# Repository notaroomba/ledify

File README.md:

<h1 align="center">
  <br>
  
</h1>

<h4 align="center">
A super small addressable LED controller with USB-C PD up to 100W, a switchable 5V/12V output and Bluetooth!
</h4>

<div align="center">

</div>

<p align="center">
  <a href="#key-features">Key Features</a> •
  <a href="#pcb">PCB</a> •
  <a href="#firmware">Firmware</a> •
  <a href="#credits">Credits</a> •
  <a href="#license">License</a>
</p>

## Key Features

- **ESP32-C6** microcontroller with Wi-Fi 6 and Bluetooth LE
- **16MB flash** (W25Q128JVP)
- **USB-C PD** up to 100W with the FUSB302B
- **Switchable 5V/12V LED output** from a 10A buck converter (LM61495), selected in software
- **Addressable LED pads** (VCC / SIG / GND) for WS2812B, WS2811 and WS2815 strips
- **IMU and Barometer** - BMI323 (6-axis) and BMP581 pressure sensor
- **Ambient light sensor** (OPT4001) for automatic brightness
- **I2S microphone** (ICS-43434) for sound-reactive effects
- **PCB trace antenna** with an impedance matching network
- **3.3V buck converter** (AP63203) for the logic side
- **ESD protection** on the USB data lines
- **Reset and boot buttons** and a mounting hole
- **4-layer PCB** design with optimized RF layout and routing

## PCB

Designed in KiCad with attention to RF design and high current power delivery. The board is 4 layers with a solid ground plane under the ESP32, the flash and the antenna feed, and the LED buck follows the layout in the LM61495 datasheet.

### Schematic

### Layout

### Pinout

| GPIO | Net        | Function                                  |
| ---- | ---------- | ----------------------------------------- |
| 2    | LED_SW_V   | LED voltage select (low = 5V, high = 12V) |
| 3    | LED_ENABLE | LED buck enable                           |
| 5    | LED_CON    | LED data (SIG pad)                        |
| 6    | MIC_OUT    | Microphone I2S data                       |
| 22   | MIC_CS     | Microphone I2S word select                |
| 23   | MIC_SCK    | Microphone I2S bit clock                  |
| 10   | I2C_SDA    | I2C data (FUSB302B, OPT4001)              |
| 11   | I2C_SCL    | I2C clock (FUSB302B, OPT4001)             |
| 16   | USB_PD_INT | FUSB302B interrupt                        |
| 18   | SPI_MISO   | Sensor SPI                                |
| 19   | SPI_MOSI   | Sensor SPI                                |
| 20   | SPI_SCK    | Sensor SPI                                |
| 21   | CS_IMU     | BMI323 chip select                        |
| 7    | CS_BARO    | BMP581 chip select                        |
| 12   | DN         | USB D-                                    |
| 13   | DP         | USB D+                                    |
| 9    | CHIP_BOOT  | Boot button                               |
| 8    | -          | Strapping pin, pulled up to 3V3           |

### Next revision

Rev 1 works; these are the changes queued for rev 2, each with the reason it is worth a spin of the board.

| Change | Why | How |
| --- | --- | --- |
| Measure the strip current | The power limit and the warnings are arithmetic from the frame; a measurement catches strips that draw more than the model and lets the firmware show real watts | INA226 (I2C, address 0x40 next to the FUSB302 at 0x22 and the OPT4001) with a 2 mΩ 2512 shunt high side on the LED rail after the buck (10 A gives 20 mV, 1 mA resolution; 0.2 W in the shunt). Its VBUS pin reads the rail, so it also sees the 12 V setting. ALERT to GPIO14 for an over-current interrupt |
| Second data output | Two strips from one board, or a strip fed from both ends with the data going into each half | A second SIG pad on GPIO17 (a second RMT channel in firmware). Both outputs through a 74AHCT1G125 each: 3.3 V data into 5 V pixels is out of spec today and works only over short leads |
| 5.2 V setting for long strips | A one-end-fed 5 V strip sags towards the far end and goes warm; starting 0.2 V higher is what long-strip supplies do | 499 kΩ from U6 FB to the drain of a 2N7002, gate from GPIO0 with a 100 kΩ pull-down. In parallel with the 24.9 kΩ bottom resistor it makes 23.7 kΩ, so 1.0 V × (1 + 100/23.7) = 5.22 V on command; the 12 V setting (14.3 kΩ switched in by Q1) is untouched |
| Power injection pads | The real fix for the sag is a second feed into the far end, and it needs a 10 A home on the board | A second VCC/GND pad pair next to the first, both on the wide copper of the LED rail |
| A user button | The BOOT button already toggles the output in firmware, but it sits under the case and shares the strapping pin | A button on GPIO1 with its own pull-up, away from the strapping pins |
| Microphone port | Board 1's ICS-43434 passes the electrical checks but hears nothing: the acoustic port is suspected | Confirm the port hole in the copper and solder mask under the mic, and keep the mic away from the buck inductor |

Free GPIOs after rev 1: 0, 1, 14, 17 (4 and 15 are strapping pins). The feedback network today: 100 kΩ top, 24.9 kΩ bottom, 1.0 V reference, 5.02 V; Q1 adds 14.3 kΩ in parallel for 12.0 V.

### JLCPCB Quote

## Firmware

The firmware in [`firmware/`](firmware/) is an ESP-IDF v6.1 project with drivers for everything on the board: USB-PD negotiation on the FUSB302B, the LED strip, the light sensor, IMU, barometer and microphone. It takes the same text commands from three places: the USB serial console, Bluetooth (it advertises as `Ledify` with the Nordic UART service, so nRF Connect or Bluefruit Connect work) and MQTT. Point it at a Wi-Fi network and a broker and it shows up in Home Assistant on its own as a light with eight effects (solid, rainbow, temperature, spectrum, meter, sound, VU, pulse), an auto-brightness switch, sliders for the pixel count and the sound, light and temperature tunables, a chip-type select and illuminance, temperature, pressure and sound sensors. The colour source, brightness source and overlay can also be mixed freely, so a rainbow VU meter that dims in a dark room is three commands. Brightness is capped automatically to what the USB-PD contract can supply, so a long strip on a laptop port dims instead of browning out.

| Command               | Action                                                                 |
| --------------------- | ---------------------------------------------------------------------- |
| `on` / `off`          | LED buck on or off                                                     |
| `rgb R G B`           | Fills the strip with a color (0-255 each)                              |
| `level N`             | Brightness cap (0-255)                                                 |
| `count N`             | How many pixels to drive (up to 1000, also a slider in Home Assistant) |
| `type ws2812`         | Chip type: `ws2812` (B/C/D/E, WS2813, WS2815), `ws2811`, `sk6812`, `sk6812w`, `ws2816` |
| `mode NAME`           | Preset, also the Home Assistant effect: `solid`, `rainbow`, `temp` (blue-white-red from the temperature), `spectrum` (bass/mid/treble bars), `meter`, `sound`, `vu`, `pulse` |
| `color` / `bright` / `overlay` | Mix your own: colour source, brightness source (`level` or `sound`), overlay (`none`, `vu`, `pulse`) |
| `auto on` / `auto off` | Brightness follows the ambient light sensor, off below a night threshold |
| `gain N`, `lux LO HI`, `night N`, `temp LO HI` | Saved tunables for the sound, light and temperature styles; `temp 21.5` feeds a temperature in |
| `volt 5` / `volt 12`  | Selects the output voltage, turns the output off first. 12V needs a 15V+ PD contract |
| `status`              | JSON with the PD contract, network state, lux, temperature, pressure, motion and sound level |
| `pd` / `net`          | The charger's offered voltages / Wi-Fi and MQTT state                  |
| `wifi SSID PASS`      | Saves the Wi-Fi credentials and restarts                               |
| `mqtt URL USER PASS`  | Saves the broker and restarts                                          |
| `ota URL`             | Updates the firmware over Wi-Fi, with automatic rollback               |

The output always boots at 5V and off, and the board asks the charger for the highest voltage up to 20V as soon as it starts. Credentials, the strip length, the chip type and the tunables are stored in the ESP32's NVS partition, never in the code. SIG is 3.3V logic going to the strip's DIN; the wiring notes, MQTT topics and the Mosquitto-on-Railway broker setup are in [`firmware/README.md`](firmware/README.md).

### Building and flashing

```bash
cd firmware
source ~/.espressif/tools/activate_idf_v6.1.sh
idf.py build
idf.py -p /dev/cu.usbmodem2101 flash monitor
```

## Credits

This project uses:

- [KiCad](https://www.kicad.org/)
- [Blender](https://www.blender.org/) for 3D renders
- [MicroPython](https://micropython.org/)

## You may also like...

- [Cyberboard](https://github.com/NotARoomba/cyberboard) – A Raspberry Pi Pico-sized STM32 development board
- [CyberCard](https://github.com/NotARoomba/CyberCard) – A Cyberpunk themed NFC hacker card
- [Ember](https://github.com/NotARoomba/ember) – USB-C PD Powered Hotplate
- [Trace](https://github.com/NotARoomba/trace) – An ruler for engineers
- [Athena](https://github.com/NotARoomba/athena) – A flight controlelr with a triple MCU architecture

## License

MIT

---

> [notaroomba.dev](https://notaroomba.dev) &nbsp;&middot;&nbsp;
> GitHub [@NotARoomba](https://github.com/NotARoomba) &nbsp;&middot;&nbsp;

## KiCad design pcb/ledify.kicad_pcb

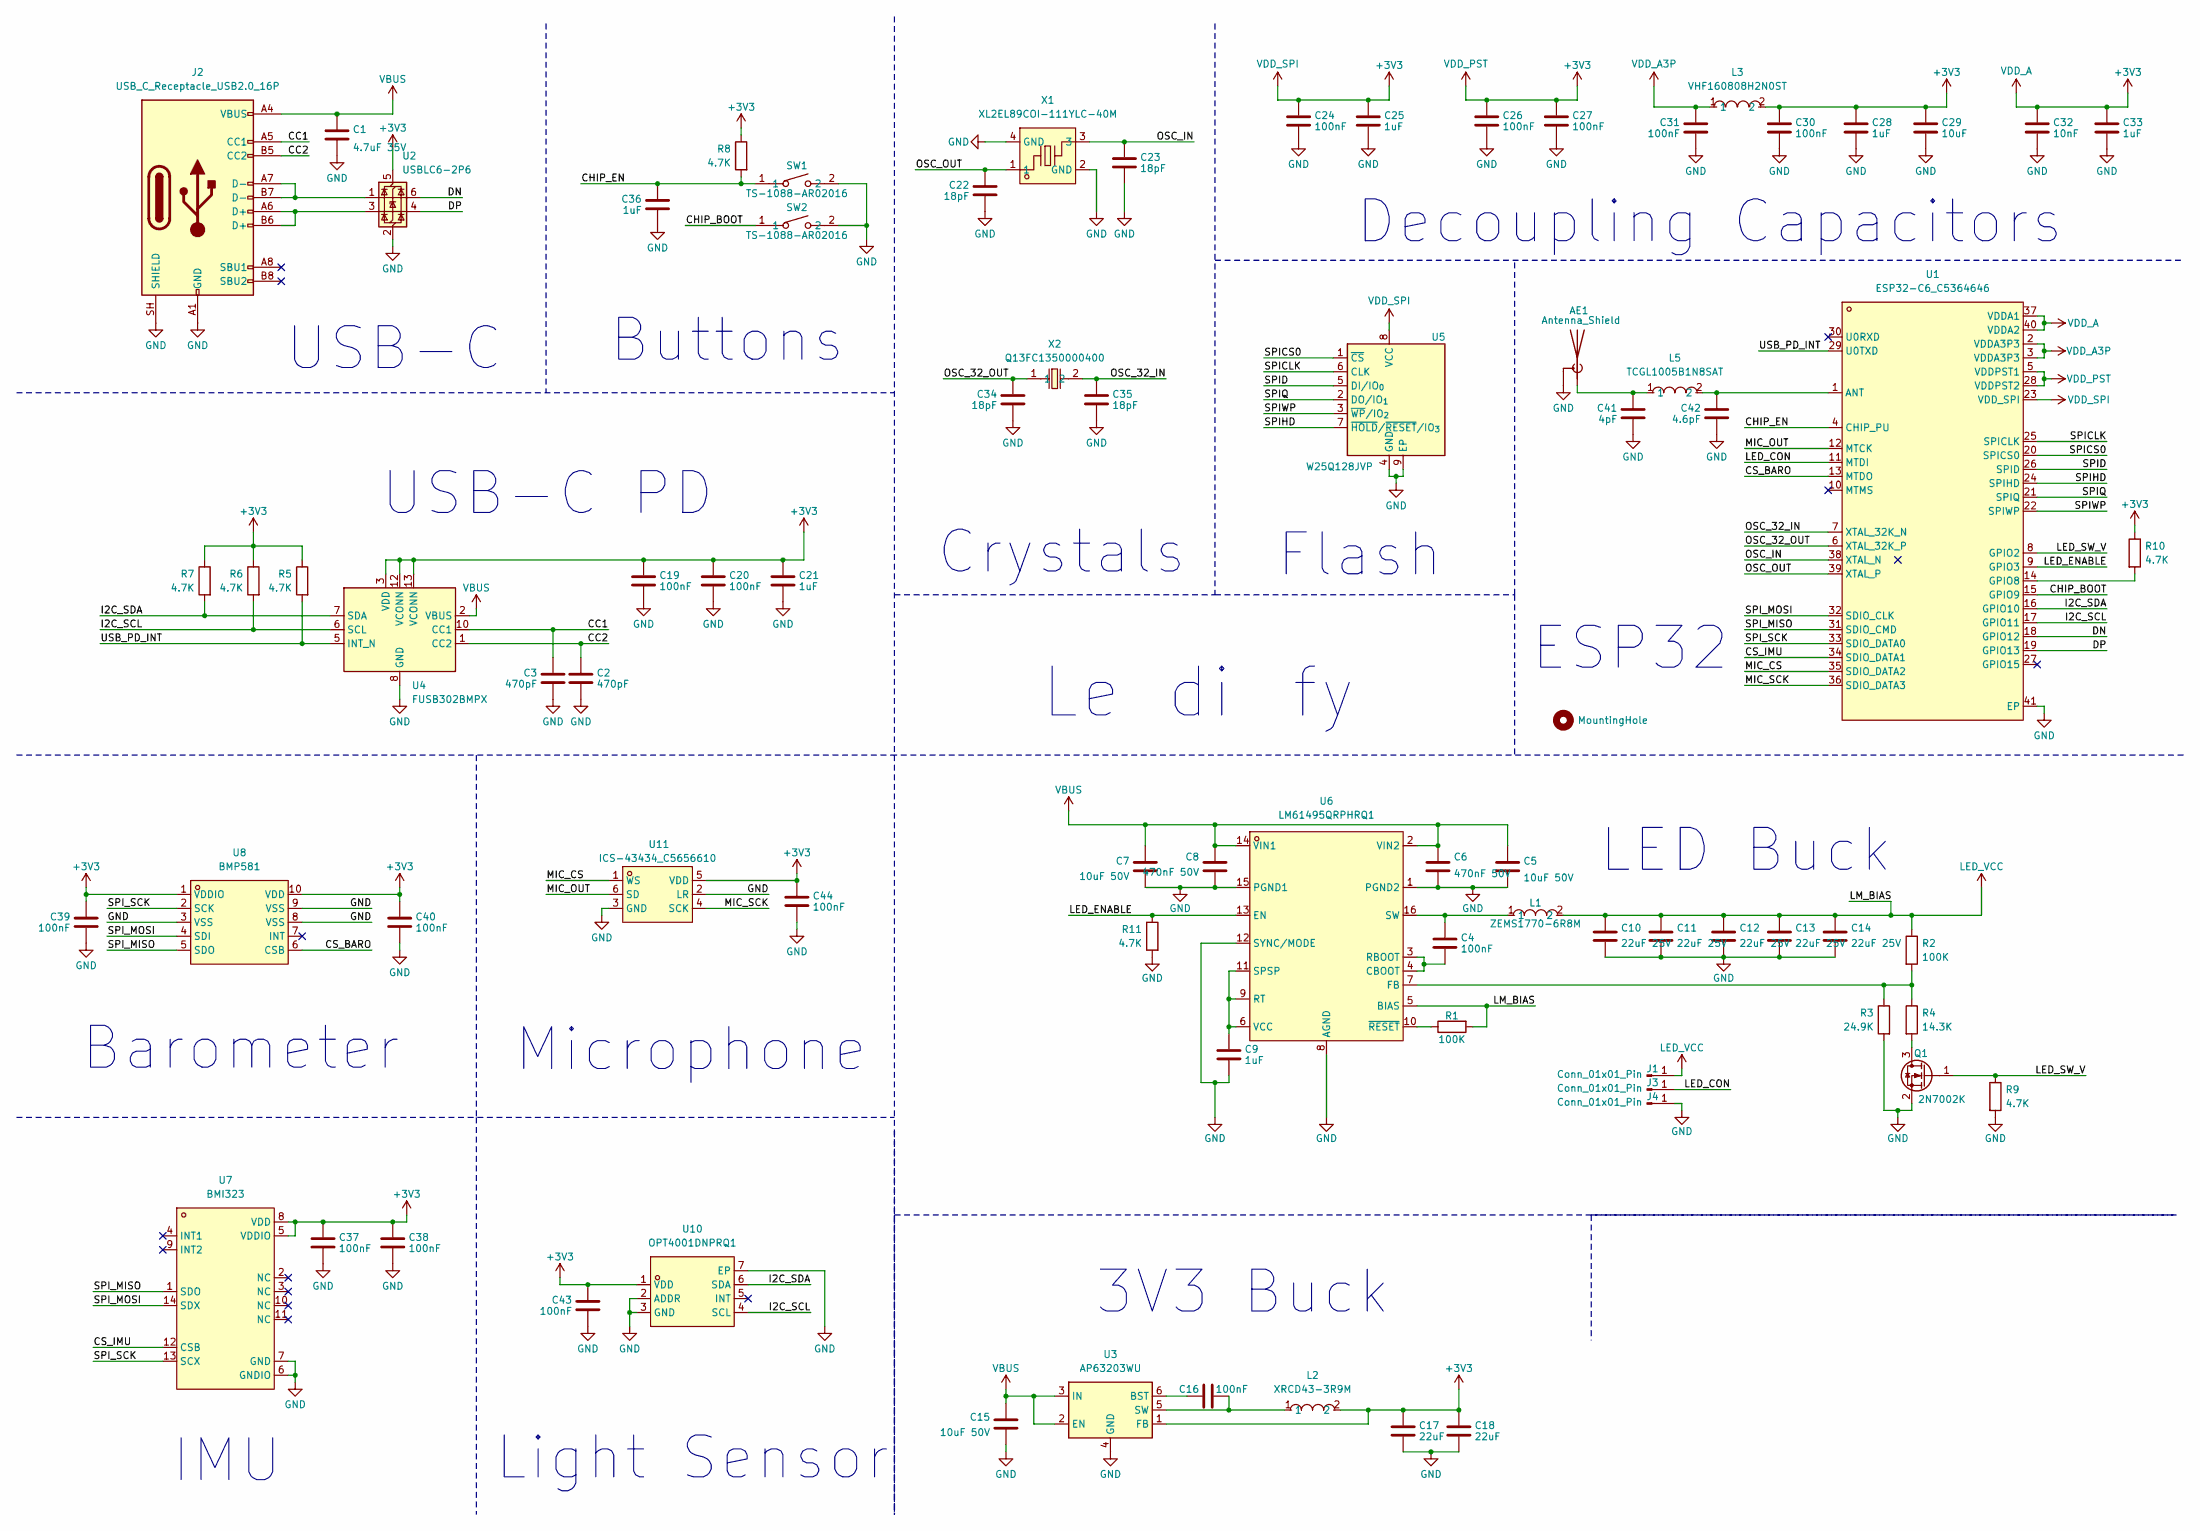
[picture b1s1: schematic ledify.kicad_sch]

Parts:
AE1: Antenna_Shield; Texas_SWRA117D_2.4GHz_Right
C1: 4.7uF 35V; C_0603_1608Metric; LCSC C307467
C2, C3: 470pF; C_0402_1005Metric; LCSC C76971
C4: 100nF; C_0402_1005Metric_Pad0.74x0.62mm_HandSolder
C5, C7, C15: 10uF 50V; C_0805_2012Metric; LCSC C440198
C6, C8: 470nF 50V; C_0603_1608Metric; LCSC C77572
C9: 1uF; C_0603_1608Metric
C10, C11, C12, C13, C14: 22uF 25V; C_1210_3225Metric; LCSC C309062
C16, C19, C20, C24, C26, C27, C30, C31, C37, C38, C39, C40, C43, C44: 100nF; C_0402_1005Metric
C17, C18: 22uF; C_0805_2012Metric
C21, C25, C28, C33, C36: 1uF; C_0402_1005Metric
C22, C23, C34, C35: 18pF; C_0402_1005Metric; LCSC C1549
C29: 10uF; C_0603_1608Metric
C32: 10nF; C_0402_1005Metric
C41: 4pF; C_0402_1005Metric; LCSC C541337
C42: 4.6pF; C_0402_1005Metric; LCSC C1855288
H1: MountingHole; MountingHole_2.2mm_M2_Pad_Via
J1, J3, J4: Conn_01x01_Pin; SolderWirePad_1x01_SMD_3x6mm
J2: USB_C_Receptacle_USB2.0_16P; USB_C_Receptacle_HCTL_HC-TYPE-C-16P-01A; LCSC C2894897
L1: ZEMS1770-6R8M; IND-SMD_L17.5-W17.5_SLO1770H; MPN ZEMS1770-6R8M; LCSC Part C41438687
L2: XRCD43-3R9M; IND-SMD_L4.0-W3.2_XRCD43; MPN XRCD43-3R9M; LCSC Part C5289397
L3: VHF160808H2N0ST; L0603; MPN VHF160808H2N0ST; LCSC Part C395081
L5: TCGL1005B1N8SAT; L0402; MPN TCGL1005B1N8SAT; LCSC Part C52109814
Q1: 2N7002K; SOT-23
R1, R2: 100K; R_0402_1005Metric
R3: 24.9K; R_0402_1005Metric
R4: 14.3K; R_0402_1005Metric; LCSC C25855
R5, R6, R7, R8, R9, R10, R11: 4.7K; R_0402_1005Metric
SW1, SW2: TS-1088-AR02016; SW-SMD_L3.9-W3.0-P4.45; MPN TS-1088-AR02016; LCSC Part C720477
U1: ESP32-C6_C5364646; QFN-40_L5.0-W5.0-P0.40-TL-EP3.3; MPN ESP32-C6; LCSC Part C5364646
U2: USBLC6-2P6; SOT-666
U3: AP63203WU; TSOT-23-6; LCSC C780769
U4: FUSB302BMPX; WQFN-14-1EP_2.5x2.5mm_P0.5mm_EP1.45x1.45mm; LCSC C132291
U5: W25Q128JVP; WSON-8-1EP_6x5mm_P1.27mm_EP3.4x4.3mm; LCSC C2441427
U6: LM61495QRPHRQ1; VQFN-16_L4.5-W3.5-P0.50-TL_TI_RPH; MPN LM61495QRPHRQ1; LCSC Part C3188410
U7: BMI323; LGA-14_L3.0-W2.5-P0.50-TL_QMI8658A; MPN BMI323; LCSC Part C5368700
U8: BMP581; LGA-10_L2.0-W2.0-P0.50-TL_BMP581; MPN BMP581; LCSC Part C5362283
U10: OPT4001DNPRQ1; USON-6_L2.0-W2.0-P0.65-BL-EP; MPN OPT4001DNPRQ1; LCSC Part C20199903
U11: ICS-43434_C5656610; MIC-SMD_6P-L3.5-W2.7-P0.90-BL; MPN ICS-43434; LCSC Part C5656610
X1: XL2EL89COI-111YLC-40M; CRYSTAL-SMD_4P-L3.2-W2.5-BL; MPN XL2EL89COI-111YLC-40M; LCSC Part C18214314
X2: Q13FC1350000400; FC-135R_L3.2-W1.5; MPN Q13FC13500004; LCSC Part C32346

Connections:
+3V3: C17.1, C18.1, C19.1, C20.1, C21.1, C24.1, C25.1, C26.1, C27.1, C28.1, C29.1, C30.1, C32.1, C33.1, C37.1, C38.1, C39.1, C40.1, C43.1, C44.1, L2.2, L3.2, R5.1, R6.1, R7.1, R8.1, R10.1, U1.5 (VDDPST1), U1.23 (VDD_SPI), U1.28 (VDDPST2), U1.37 (VDDA1), U1.40 (VDDA2), U2.5 (VBUS), U3.1 (FB), U4.3 (VDD), U4.4 (VDD), U4.12 (VCONN), U4.13 (VCONN), U5.8 (VCC), U7.5 (VDDIO), U7.8 (VDD), U8.1 (VDDIO), U8.10 (VDD), U10.1 (VDD), U11.5 (VDD)
/CC1: C3.1, J2.A5 (CC1), U4.10 (CC1), U4.11 (CC1)
/CC2: C2.1, J2.B5 (CC2), U4.1 (CC2), U4.14 (CC2)
/CHIP_BOOT: SW2.1, U1.15 (GPIO9)
/CHIP_EN: C36.1, R8.2, SW1.1, U1.4 (CHIP_PU)
/CS_BARO: U1.13 (MTDO), U8.6 (CSB)
/CS_IMU: U1.34 (SDIO_DATA1), U7.12 (CSB)
/DN: U1.18 (GPIO12), U2.6 (I/O1)
/DP: U1.19 (GPIO13), U2.4 (I/O2)
/I2C_SCL: R6.2, U1.17 (GPIO11), U4.6 (SCL), U10.4 (SCL)
/I2C_SDA: R7.2, U1.16 (GPIO10), U4.7 (SDA), U10.6 (SDA)
/LED_CON: J3.1 (Pin_1_1), U1.11 (MTDI)
/LED_ENABLE: R11.1, U1.9 (GPIO3), U6.13 (EN)
/LED_SW_V: Q1.1 (G), R9.1, U1.8 (GPIO2)
/MIC_CS: U1.35 (SDIO_DATA2), U11.1 (WS)
/MIC_OUT: U1.12 (MTCK), U11.6 (SD)
/MIC_SCK: U1.36 (SDIO_DATA3), U11.4 (SCK)
/OSC_32_IN: C35.1, U1.7 (XTAL_32K_N), X2.2
/OSC_32_OUT: C34.1, U1.6 (XTAL_32K_P), X2.1
/OSC_IN: C23.1, U1.38 (XTAL_N), X1.3
/OSC_OUT: C22.1, U1.39 (XTAL_P), X1.1
/SPICLK: U1.25 (SPICLK), U5.6 (CLK)
/SPICS0: U1.20 (SPICS0), U5.1 (~CS)
/SPID: U1.26 (SPID), U5.5 (DI/IO_{0})
/SPIHD: U1.24 (SPIHD), U5.7 (~HOLD/~RESET/IO_{3})
/SPIQ: U1.21 (SPIQ), U5.2 (DO/IO_{1})
/SPIWP: U1.22 (SPIWP), U5.3 (~WP/IO_{2})
/SPI_MISO: U1.31 (SDIO_CMD), U7.1 (SDO), U8.5 (SDO)
/SPI_MOSI: U1.32 (SDIO_CLK), U7.14 (SDX), U8.4 (SDI)
/SPI_SCK: U1.33 (SDIO_DATA0), U7.13 (SCX), U8.2 (SCK)
/USB_PD_INT: R5.2, U1.29 (U0TXD), U4.5 (INT_N)
GND: AE1.2 (Shield), C1.2, C2.2, C3.2, C5.2, C6.2, C7.2, C8.2, C9.2, C10.2, C11.2, C12.2, C13.2, C14.2, C15.2, C17.2, C18.2, C19.2, C20.2, C21.2, C22.2, C23.2, C24.2, C25.2, C26.2, C27.2, C28.2, C29.2, C30.2, C31.2, C32.2, C33.2, C34.2, C35.2, C36.2, C37.2, C38.2, C39.2, C40.2, C41.2, C42.2, C43.2, C44.2, J2.A1 (GND), J2.A12 (GND), J2.B1 (GND), J2.B12 (GND), J2.SH (SHIELD), J4.1 (Pin_1_1), Q1.2 (S), R3.2, R9.2, R11.2, SW1.2, SW2.2, U1.41 (EP), U2.2 (GND), U3.4 (GND), U4.8 (GND), U4.9 (GND), U4.15 (GND), U5.4 (GND), U5.9 (EP), U6.1 (PGND2), U6.8 (AGND), U6.12 (SYNC/MODE), U6.15 (PGND1), U7.6 (GNDIO), U7.7 (GND), U8.3 (VSS), U8.8 (VSS), U8.9 (VSS), U10.2 (ADDR), U10.3 (GND), U10.7 (EP), U11.2 (LR), U11.3 (GND), X1.2 (GND), X1.4 (GND)
LED_VCC: C10.1, C11.1, C12.1, C13.1, C14.1, J1.1 (Pin_1_1), L1.2, R1.2, R2.1, U6.5 (BIAS)
unnamed: AE1.1 (A), C41.1, L5.1
unnamed: J2.A6 (D+), J2.B6 (D+), U2.3 (I/O2)
unnamed: J2.A7 (D-), J2.B7 (D-), U2.1 (I/O1)
unnamed: Q1.3 (D), R4.2
unnamed: C42.1, L5.2, U1.1 (ANT)
unnamed: R10.2, U1.14 (GPIO8)
unnamed: C16.1, U3.6 (BST)
unnamed: C16.2, L2.1, U3.5 (SW)
unnamed: C4.2, U6.3 (RBOOT), U6.4 (CBOOT)
unnamed: R2.2, R3.1, R4.1, U6.7 (FB)
unnamed: C9.1, U6.6 (VCC), U6.9 (RT), U6.11 (SPSP)
unnamed: C4.1, L1.1, U6.16 (SW)
unnamed: R1.1, U6.10 (~RESET)
VBUS: C1.1, C5.1, C6.1, C7.1, C8.1, C15.1, J2.A4 (VBUS), J2.A9 (VBUS), J2.B4 (VBUS), J2.B9 (VBUS), U3.2 (EN), U3.3 (IN), U4.2 (VBUS), U6.2 (VIN2), U6.14 (VIN1)
VDD_A3P: C31.1, L3.1, U1.2 (VDDA3P3), U1.3 (VDDA3P3)

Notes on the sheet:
ESP32
IMU
Buttons
USB-C
Barometer
Decoupling Capacitors
Microphone
3V3 Buck
LED Buck
Light Sensor
Crystals
USB-C PD
Flash

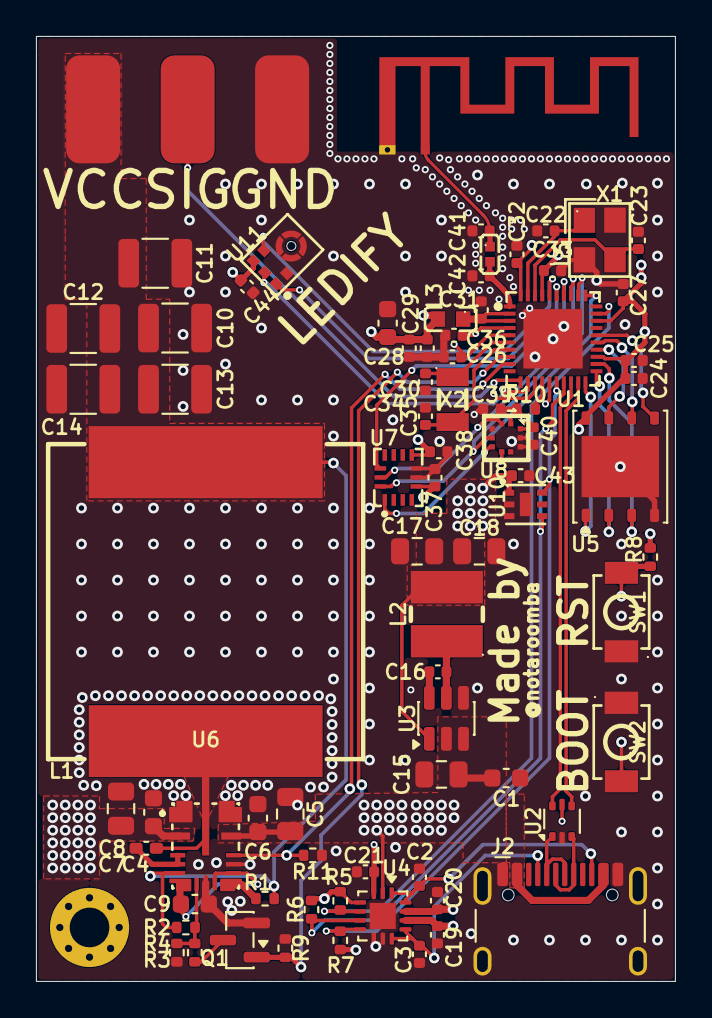
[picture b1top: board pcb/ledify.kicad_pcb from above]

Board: 4 copper layers, 35.5 x 52.5 mm, 80 parts (0 on the bottom side), 48 nets.

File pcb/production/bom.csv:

Designator,Footprint,Quantity,Value,LCSC Part #
AE1,Texas_SWRA117D_2.4GHz_Right,1,Antenna_Shield,
C1,0603,1,"4.7uF
35V",C307467
"C10, C11, C12, C13, C14",1210,5,"22uF
25V",C309062
"C15, C5, C7",0805,3,"10uF
50V",C440198
"C16, C19, C20, C24, C26, C27, C30, C31, C37, C38, C39, C4, C40, C43, C44",0402,15,100nF,
"C17, C18",0805,2,22uF,
"C2, C3",0402,2,470pF,C76971
"C21, C25, C28, C33, C36",0402,5,1uF,
"C22, C23, C34, C35",0402,4,18pF,C1549
C29,0603,1,10uF,
C32,0402,1,10nF,
C41,0402,1,4pF,C541337
C42,0402,1,4.6pF,C1855288
"C6, C8",0603,2,"470nF
50V",C77572
C9,0603,1,1uF,
"J1, J3, J4",SolderWirePad_1x01_SMD_3x6mm,3,Conn_01x01_Pin,
J2,USB_C_Receptacle_HCTL_HC-TYPE-C-16P-01A,1,USB_C_Receptacle_USB2.0_16P,C2894897
L1,IND-SMD_L17.5-W17.5_SLO1770H,1,ZEMS1770-6R8M,C41438687
L2,IND-SMD_L4.0-W3.2_XRCD43,1,XRCD43-3R9M,C5289397
L3,L0603,1,VHF160808H2N0ST,C395081
L5,L0402,1,TCGL1005B1N8SAT,C52109814
Q1,SOT-23,1,2N7002K,
"R1, R2",0402,2,100K,
"R10, R11, R5, R6, R7, R8, R9",0402,7,4.7K,
R3,0402,1,24.9K,
R4,0402,1,14.3K,C25855
"SW1, SW2",SW-SMD_L3.9-W3.0-P4.45,2,TS-1088-AR02016,C720477
U1,QFN-40_L5.0-W5.0-P0.40-TL-EP3.3,1,ESP32-C6_C5364646,C5364646
U10,USON-6_L2.0-W2.0-P0.65-BL-EP,1,OPT4001DNPRQ1,C20199903
U11,MIC-SMD_6P-L3.5-W2.7-P0.90-BL,1,ICS-43434_C5656610,C5656610
U2,SOT-666,1,USBLC6-2P6,
U3,TSOT-23-6,1,AP63203WU,C780769
U4,WQFN-14-1EP_2.5x2.5mm_P0.5mm_EP1.45x1.45mm,1,FUSB302BMPX,C132291
U5,WSON-8-1EP_6x5mm_P1.27mm_EP3.4x4.3mm,1,W25Q128JVP,C2441427
U6,VQFN-16_L4.5-W3.5-P0.50-TL_TI_RPH,1,LM61495QRPHRQ1,C3188410
U7,LGA-14_L3.0-W2.5-P0.50-TL_QMI8658A,1,BMI323,C5368700
U8,LGA-10_L2.0-W2.0-P0.50-TL_BMP581,1,BMP581,C5362283
X1,CRYSTAL-SMD_4P-L3.2-W2.5-BL,1,XL2EL89COI-111YLC-40M,C18214314
X2,FC-135R_L3.2-W1.5,1,Q13FC1350000400,C32346

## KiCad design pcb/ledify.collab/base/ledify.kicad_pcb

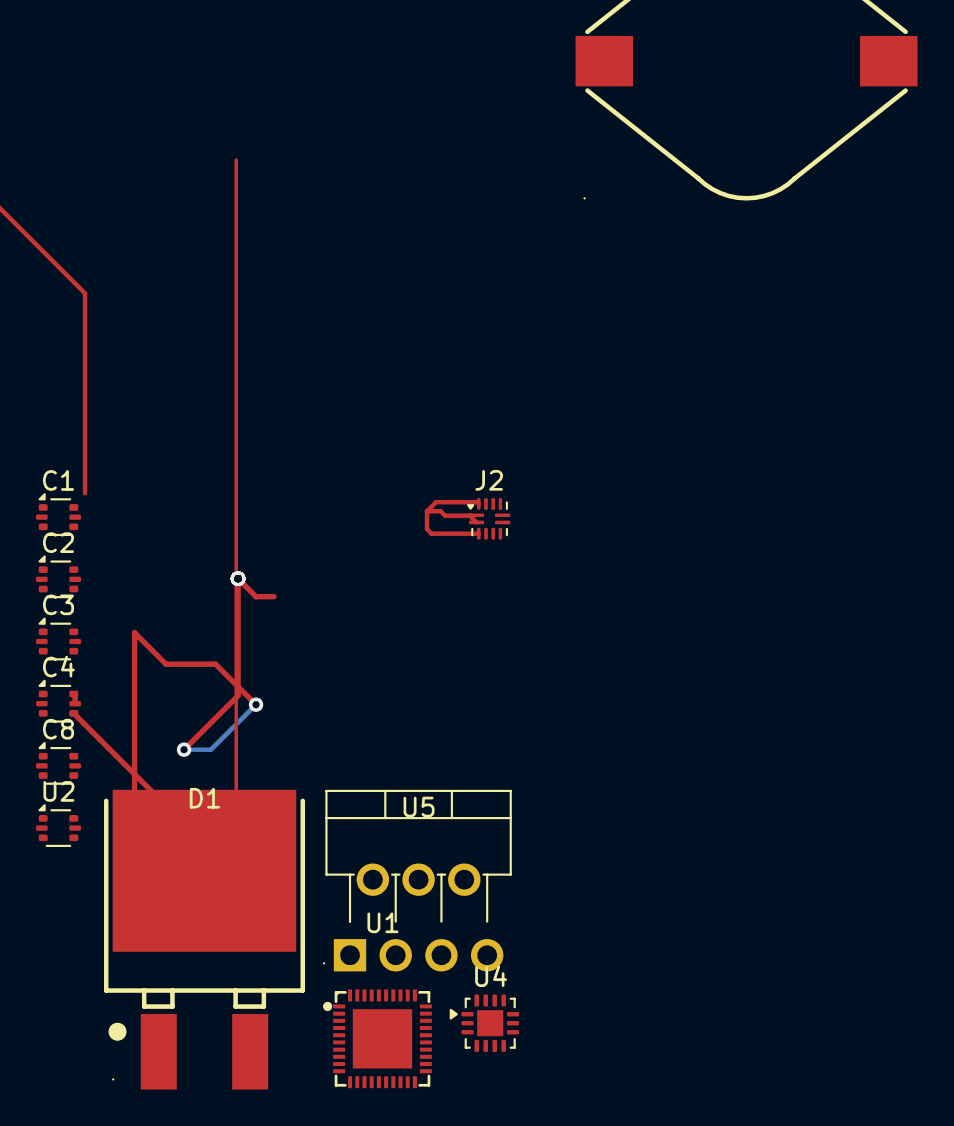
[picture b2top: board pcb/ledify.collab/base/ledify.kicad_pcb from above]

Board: 2 copper layers, 12 parts (0 on the bottom side), 7 nets.

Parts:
C1: 4.7uF; SOT-666
C2, C3, C8: 400pF; SOT-666
C4: 470nF; SOT-666
D1: VS-6TQ045STRL-M3; TO-263AB_L10.0-W9.2-P5.08-LS15.4-BL
J2: USB_C_Receptacle_USB2.0_16P; Texas_X2QFN-12_1.6x1.6mm_P0.4mm
L1: DO5022P-103MLD; IND-SMD_L18.0-W15.2
U1: ESP32-C6_C5364646; QFN-40_L5.0-W5.0-P0.40-TL-EP3.3
U2: USBLC6-2P6; SOT-666
U4: FUSB302BMPX; WQFN-14-1EP_2.5x2.5mm_P0.5mm_EP1.45x1.45mm
U5: LM2678T-5.0/NOPB; TO-220-7-L10.5-W4.5-P1.27-BL

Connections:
/CC1: C3.1, U4.10 (CC1), U4.11 (CC1)
/CC2: C2.1, U4.1 (CC2), U4.14 (CC2)
GND: C1.2, C2.2, C3.2, C4.2, D1.3 (Anode), U1.41 (EP_41), U2.2 (GND), U4.8 (GND), U4.9 (GND), U4.15 (GND), U5.4 (GND)
unnamed: C8.2, D1.2 (cathode), L1.2 (2_2), U5.1 (Switch_output)
unnamed: U4.3 (VDD), U4.4 (VDD)
unnamed: C8.1, U5.3 (CB)
VBUS: C1.1, C4.1, U2.5 (VBUS), U4.2 (VBUS), U5.2 (Input)

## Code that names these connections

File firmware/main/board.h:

#pragma once

// Ledify rev 1 pin map (ESP32-C6 GPIO numbers)
#define PIN_LED_DATA    5   // LED_CON, the SIG pad
#define PIN_LED_ENABLE  3   // LED buck enable, high = on
#define PIN_LED_12V     2   // low = 5 V, high = 12 V
#define PIN_I2C_SDA    10   // FUSB302 + OPT4001
#define PIN_I2C_SCL    11
#define PIN_PD_INT     16   // FUSB302 interrupt, polled instead
#define PIN_SPI_MISO   18
#define PIN_SPI_MOSI   19
#define PIN_SPI_SCK    20
#define PIN_CS_IMU     21   // BMI323
#define PIN_CS_BARO     7   // BMP581
#define PIN_MIC_SCK    23   // ICS-43434 bit clock
#define PIN_MIC_WS     22   // ICS-43434 word select
#define PIN_MIC_SD      6   // ICS-43434 data
#define MIC_DB_FULL_SCALE 120  // ICS-43434: 94 dB SPL reads -26 dBFS, so 0 dBFS is 120 dB SPL; ponytail: no A-weighting
#define MIC_DB_FLOOR 30        // below the mic's own noise floor the number means nothing

#define NUM_LEDS      300   // pixels driven until "count" is set
#define MAX_LEDS     1000   // most the firmware will drive (3 KB pixel buffer, 30 ms per frame)
#define PUBLISH_MS   5000   // state + sensors to MQTT this often (the panel shows them live)
#define FRAME_MS       33   // live styles redraw at 30 fps; 300 pixels take 9 ms of that on the wire
#define SOUND_FRAME_MS 16   // sound styles redraw at about 60 fps (or as fast as the wire allows on long strips)
// Per-pixel draw, FastLED's WS2812 power model at 5 V: 16/11/15 mA per channel at full, 1 mA dark. WLED's limiter
// uses the same idea with 55 mA per full-white pixel. ponytail: measure your strip and adjust if the cap is off.
#define LED_RED_MW    80
#define LED_GREEN_MW  55
#define LED_BLUE_MW   75
#define LED_DARK_MW    5
#define MIC_FEED_HOLD_MS 1000   // audio fed from the panel overrides the mic for this long after the last packet
#define LIVE_MS        100      // "live N" streams loudness/bands to MQTT this often
#define LED_BUDGET_NO_PD_MW 7500 // no PD contract: assume a 5 V 1.5 A port
#define LED_BUCK_MAX_MA 10000    // LM61495 output limit
#define LED_BUCK_EFF_PCT 85      // what makes it from the PD contract to the strip
#define PD_WANT_MV  20000   // highest PD voltage we accept
#define PD_WANT_MA   5000   // most current we ask for
#define LED_POWER_SETTLE_MS 100     // buck soft start + pixel power-on reset before the first frame
#define WIFI_NETS 6                 // the primary plus up to 5 fallbacks
#define PD_START_DELAY_MS 100   // the source starts sending capabilities right away; answer them promptly
#define PIN_BUTTON      9   // the BOOT button, free after reset: a short press toggles the output
#define FADE_MS       300   // default transition: colour and brightness changes ease over about this long
#define THERMAL_MAX_C  70   // board temperature at which the strip is fully dimmed; dimming starts 10 degrees lower
#define STREAM_TIMEOUT_MS 2500  // no DDP/E1.31 frame for this long: back to the normal styles
#define STREAM_PORT_DDP  4048
#define STREAM_PORT_E131 5568
#define FRAME_MAX_BYTES (4 + MAX_LEDS * 3)   // a picture from the panel: "LM" w h, then RGB for every pixel
#define MQTT_BUF_SIZE (FRAME_MAX_BYTES + 128) // MQTT receive buffer: the largest frame plus its topic and header
